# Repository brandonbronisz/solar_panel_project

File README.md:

# solar_panel_project
# solar_panel_project

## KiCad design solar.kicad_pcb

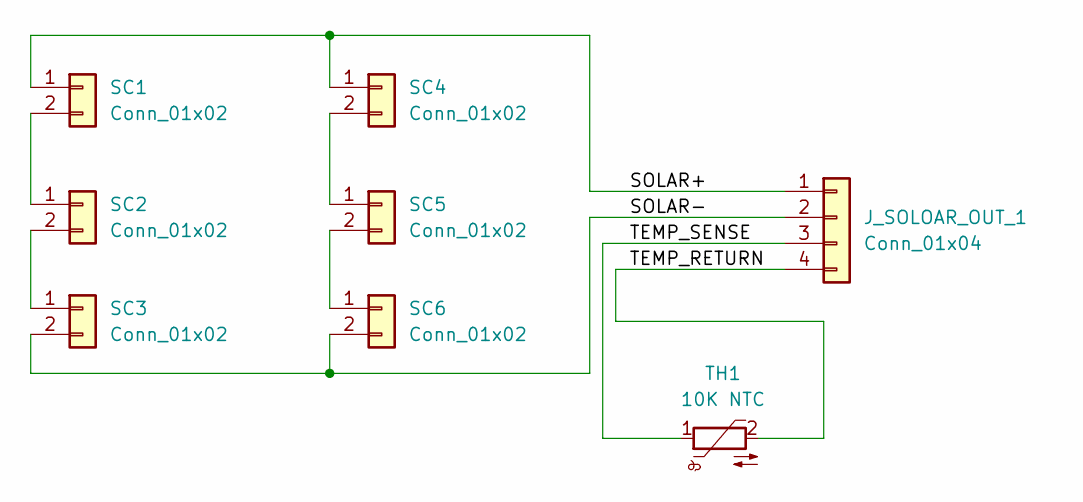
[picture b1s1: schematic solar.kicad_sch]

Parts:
J_SOLOAR_OUT_1: Conn_01x04; JST_PH_S4B-PH-K_1x04_P2.00mm_Horizontal
SC1, SC2, SC3, SC4, SC5, SC6: Conn_01x02; ANYSOLAR_KXOB201K04TF
TH1: 10K NTC; D_DO-35_SOD27_P7.62mm_Horizontal

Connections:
/SOLAR+: J_SOLOAR_OUT_1.1, SC1.1, SC4.1
/SOLAR-: J_SOLOAR_OUT_1.2, SC3.2, SC6.2
/TEMP_RETURN: J_SOLOAR_OUT_1.4, TH1.2
/TEMP_SENSE: J_SOLOAR_OUT_1.3, TH1.1
unnamed: SC1.2, SC2.1
unnamed: SC2.2, SC3.1
unnamed: SC4.2, SC5.1
unnamed: SC5.2, SC6.1

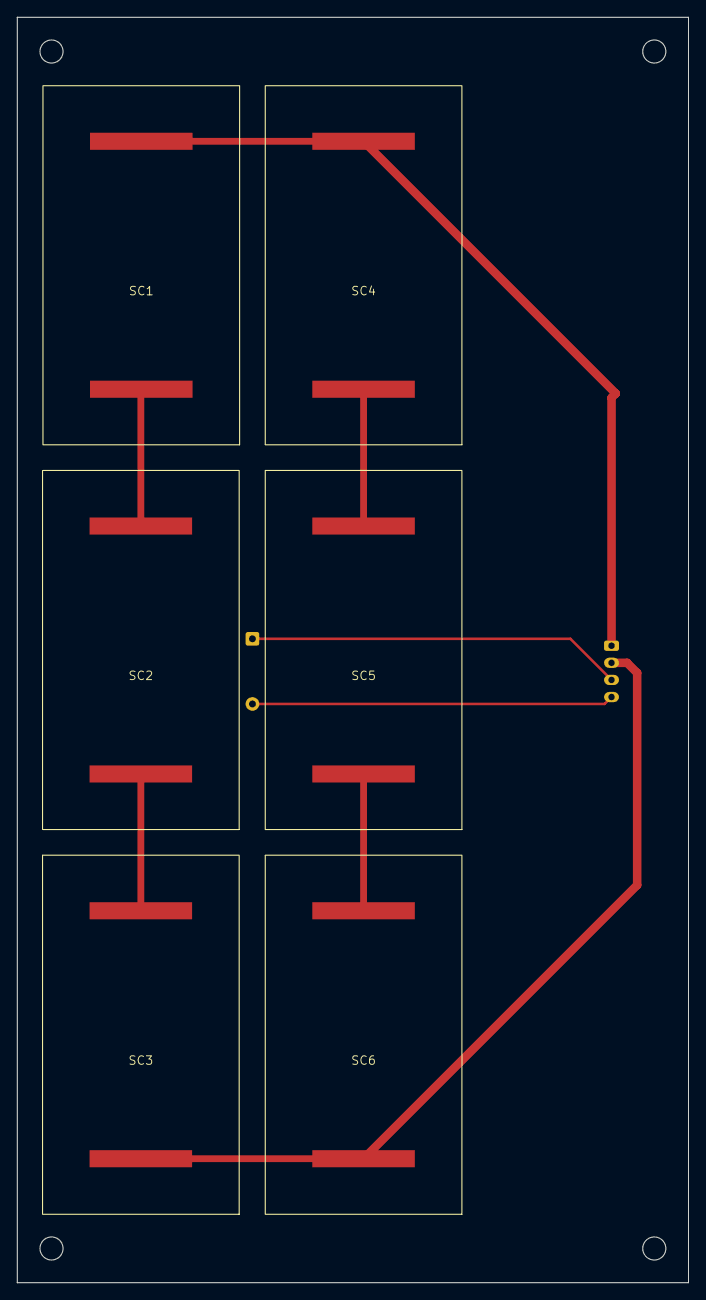
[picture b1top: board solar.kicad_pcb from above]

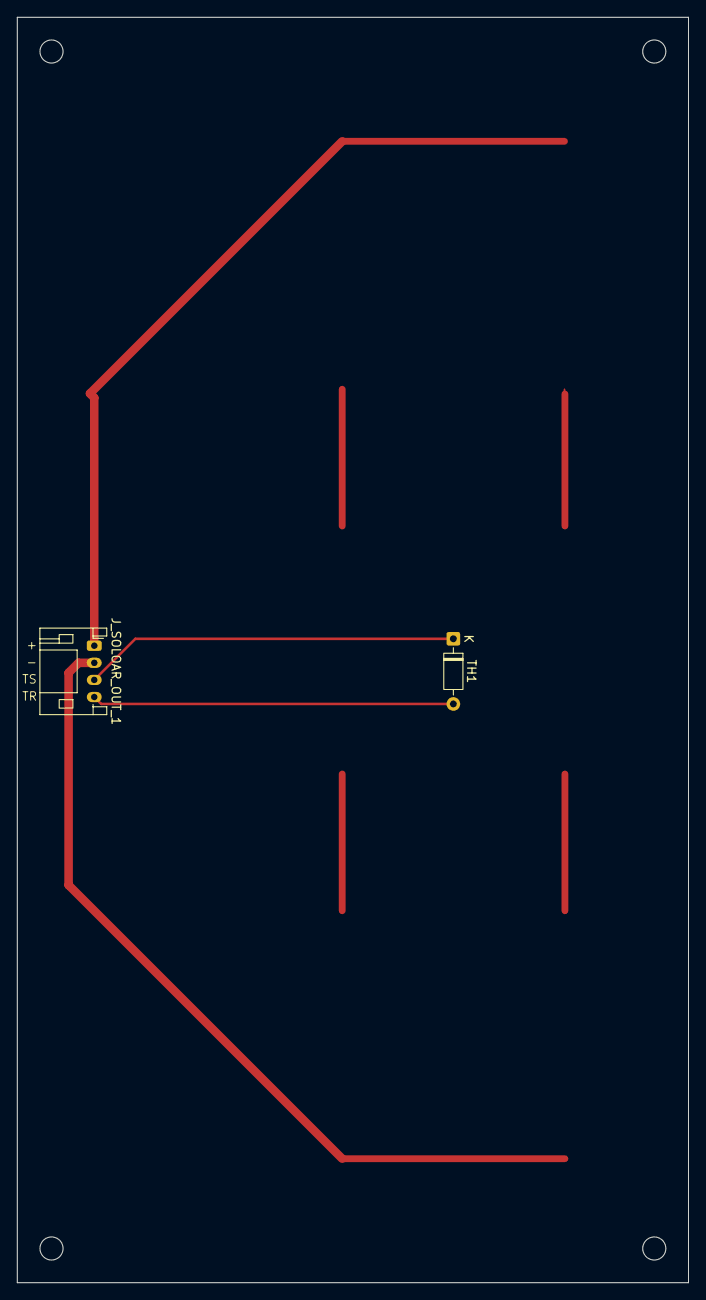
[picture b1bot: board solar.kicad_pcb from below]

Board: 2 copper layers, 78.5 x 148.0 mm, 8 parts (2 on the bottom side), 8 nets.

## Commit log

2026-04-07 init
2026-04-07 add temperature sensor
